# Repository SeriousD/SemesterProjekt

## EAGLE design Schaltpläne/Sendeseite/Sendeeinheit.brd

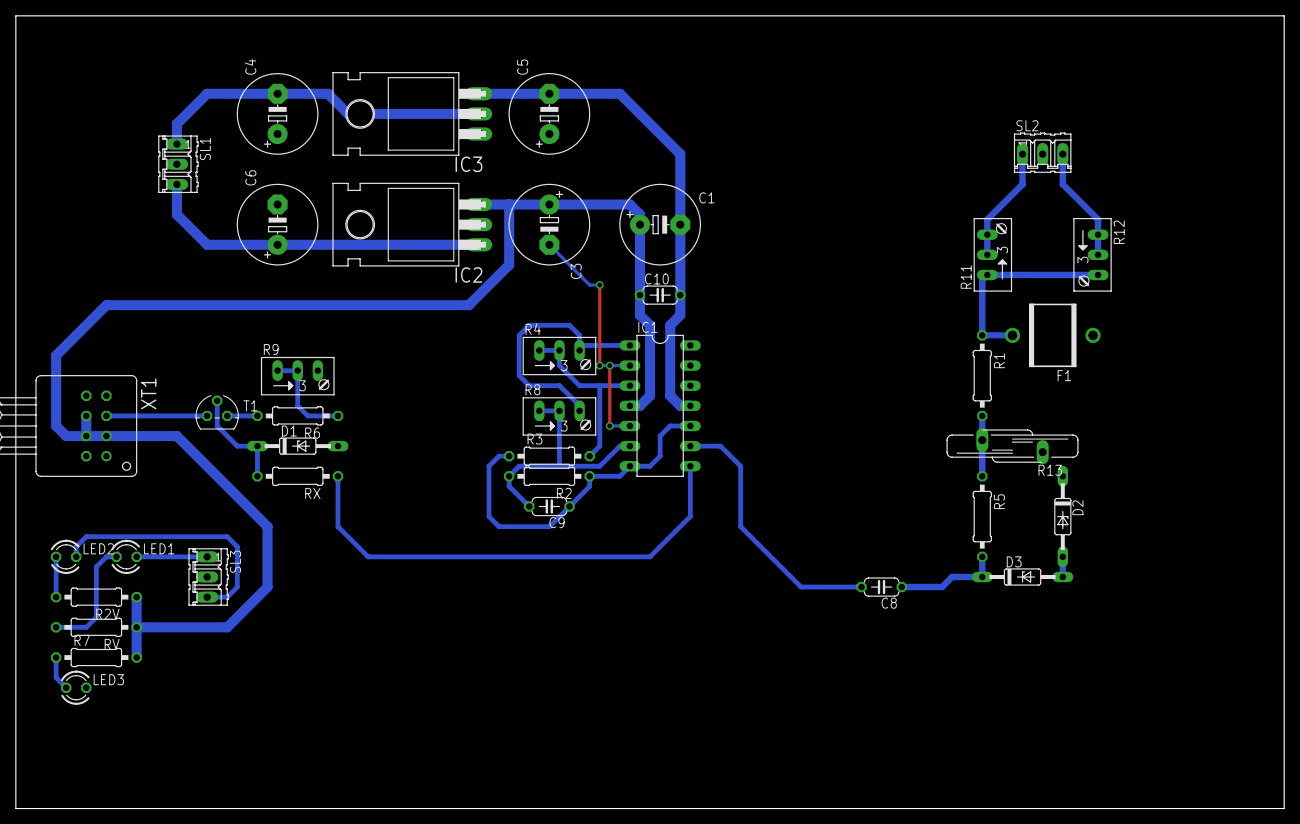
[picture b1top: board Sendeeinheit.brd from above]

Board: 2 copper layers, 160.0 x 100.0 mm, 38 parts (0 on the bottom side), 26 nets.

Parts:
C1: E5-10,5
C3, C5: 1µ; E5-10,5
C4: 300n; E5-10,5
C6: 330n; E5-10,5
C8, C10: C050-024X044
C9: 100n; C050-024X044
D1: DO35Z10
D2, D3: 7,5; DO35Z10
F1: EPCOS_N81
IC1: TL074P; DIL14
IC2: 7805T; TO220H
IC3: 7905T; TO220H
LED1, LED2, LED3: LED3MM
R1, R5: 1k; 0207/10
R2: 1M; 0207/10
R2V, R6, R7: 0207/10
R3: 50k; 0207/10
R4: 100k; RJ9W
R8: 5k; RJ9W
R9: RJ9W
R11: 50k; RJ9W
R12: 20k; RJ9W
R13: S14K11
RV: 0207/10
RX: 0207/10
SL1, SL2, SL3: 03P
T1: BC547; TO92
XT1: HFBR-1412; HFBR-X41X

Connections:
+5V: C1.+, C3.+, C10.1, IC1.4, IC2.3, R2V.1, R7.2, RV.1, XT1.2, XT1.6, XT1.7
-5V: C1.-, C5.-, C10.2, IC1.11, IC3.3
AC_IN: C8.2, IC1.9
GND: C3.-, C4.+, C5.+, C6.-, D1.A, D2.C, F1.1, IC1.2, IC1.5, IC2.2, IC3.1, LED3.K, R9.A, R13.1, SL1.2, SL2.2, SL3.2
unnamed: C6.+, IC2.1, SL1.3
unnamed: C4.-, IC3.2, SL1.1
unnamed: R12.E, R12.S, SL2.3
unnamed: R11.A, R11.S, SL2.1
unnamed: F1.2, R1.1, R11.E, R12.A
unnamed: D2.A, D3.A
unnamed: R1.2, R5.1, R13.2
unnamed: C8.1, D3.C, R5.2
unnamed: C9.2, IC1.6, R2.2, R8.E, R8.S
unnamed: LED2.K, SL3.3
unnamed: LED1.K, SL3.1
unnamed: LED2.A, R2V.2
unnamed: LED1.A, RV.2
unnamed: LED3.A, R7.1
unnamed: IC1.1, R4.A, R8.A
unnamed: IC1.3, R3.2, R4.E, R4.S
unnamed: T1.3, XT1.3
unnamed: D1.C, RX.2, T1.2
unnamed: R6.2, T1.1
unnamed: R6.1, R9.E, R9.S
PWM: IC1.8, RX.1
TRIANGLE: C9.1, IC1.7, IC1.10, R2.1, R3.1

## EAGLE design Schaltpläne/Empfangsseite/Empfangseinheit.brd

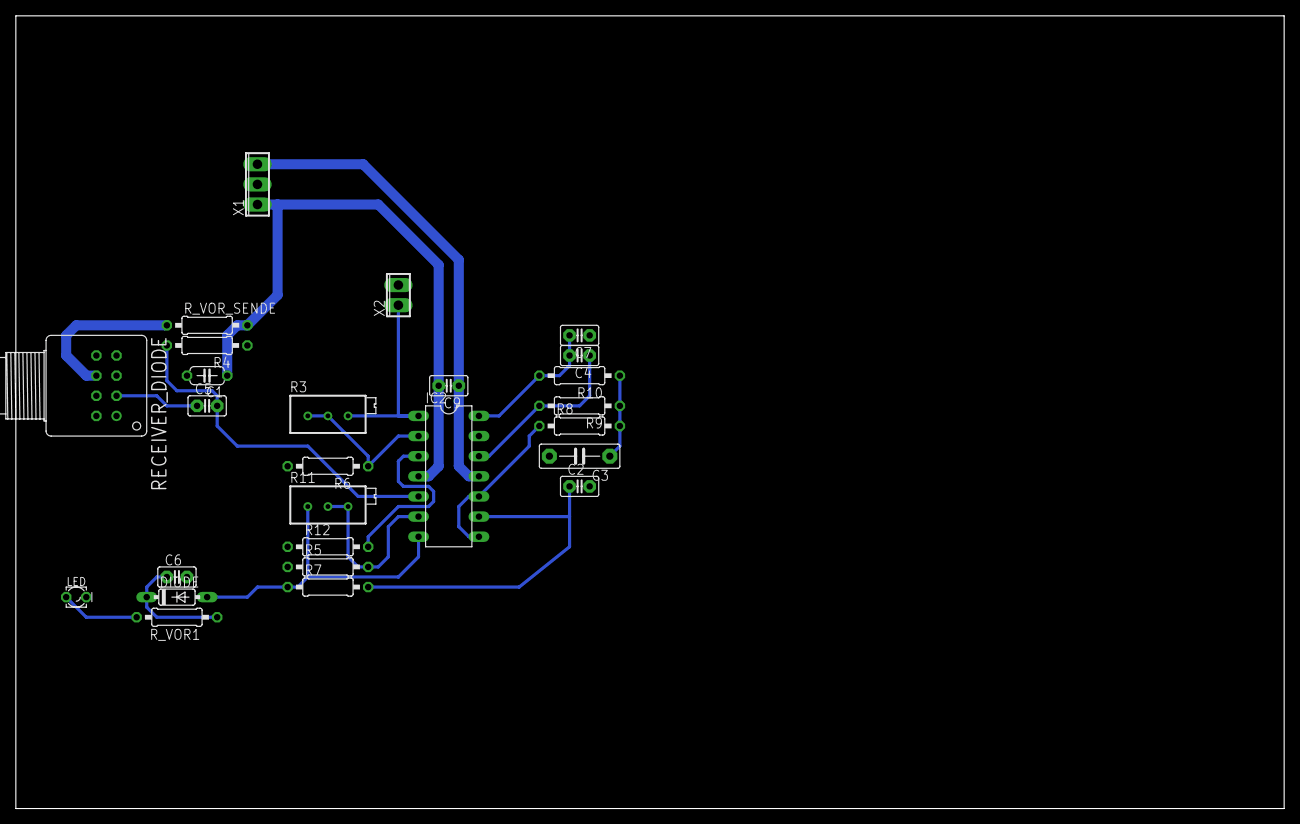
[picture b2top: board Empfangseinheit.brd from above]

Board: 2 copper layers, 160.0 x 100.0 mm, 26 parts (0 on the bottom side), 18 nets.

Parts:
C1: 22pF; C050-024X044
C2, C4, C5, C7, C9: 100nF; C2.5-2
C3: 1µF; C7.5B3
C6: 1µF; C2.5-2
DIODE: DIODE_DO35-7
IC2: TL074P; DIL14
LED: LED_LD260
R3: 50k; RTRIMT93XA
R4: 33k; 0207/10
R5, R6: 1k; 0207/10
R7: 15k; 0207/10
R8, R10: 6,8k; 0207/10
R9: 4,7k; 0207/10
R11: 500k; RTRIMT93XA
R12: 1M; 0207/10
RECEIVER_DIODE: HFBR-2416
R_VOR1: 33; 0207/10
R_VOR_SENDE: 10; 0207/10
X1: +5V,0V,-5V; 3POL254
X2: 2POL254

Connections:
FINAL_OUTPUT: IC2.1, R3.3, X2.1
FINAL_SIGNAL: IC2.2, R3.1, R3.2, R6.1
GND: C1.2, C2.2, C3.2, C6.2, IC2.13, LED.K, R4.1, R5.1, R6.2, R12.1, RECEIVER_DIODE.3, RECEIVER_DIODE.7, X1.2, X2.2
unnamed: C3.1, R8.2, R9.1, R10.1
unnamed: C4.1, IC2.12, R9.2
unnamed: C5.1, RECEIVER_DIODE.2
unnamed: IC2.6, R5.2, R11.2, R11.3
unnamed: C5.2, IC2.5, R4.2
unnamed: C2.1, IC2.9, R7.2
unnamed: C6.1, DIODE.C, R_VOR1.1
unnamed: RECEIVER_DIODE.6, R_VOR_SENDE.1
unnamed: C7.1, IC2.3, R12.2
unnamed: IC2.8, IC2.10, R8.1
unnamed: LED.A, R_VOR1.2
POST_AMP: DIODE.A, IC2.7, R7.1, R11.1
POST_FILTER: C4.2, C7.2, IC2.14, R10.2
V+: C1.1, C9.2, IC2.4, R_VOR_SENDE.2, X1.1
V-: C9.1, IC2.11, X1.3

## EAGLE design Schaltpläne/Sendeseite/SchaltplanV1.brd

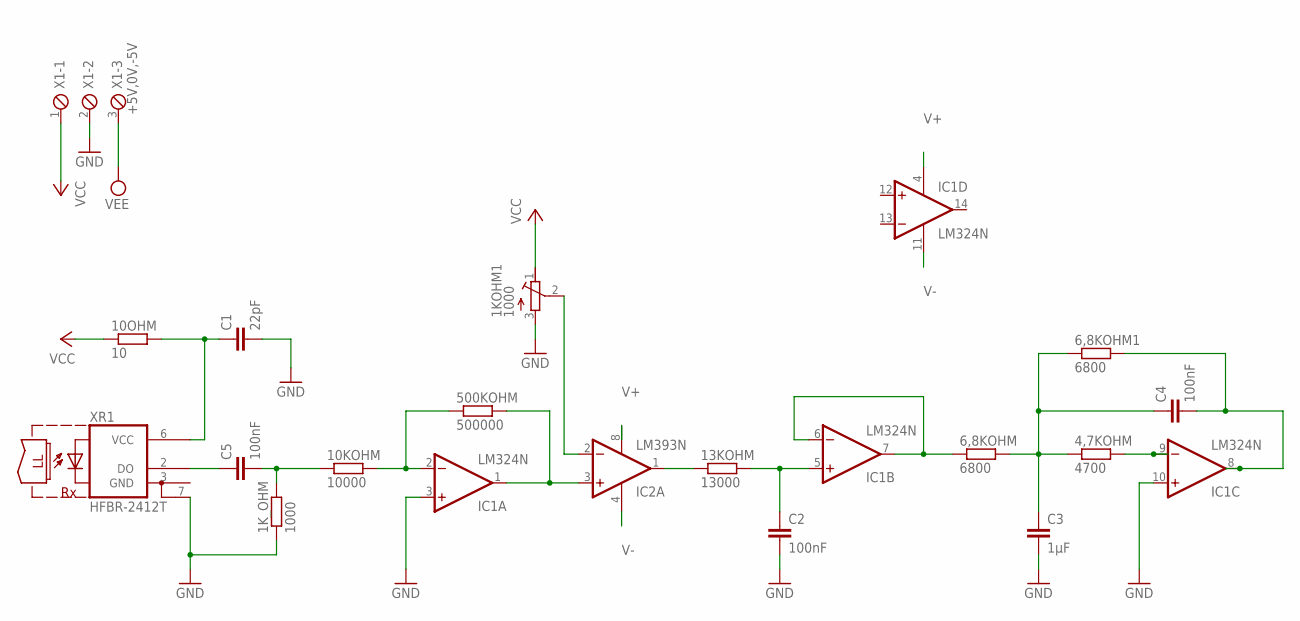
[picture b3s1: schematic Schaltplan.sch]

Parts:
1KOHM1: 1000; RTRIMT93XA
1K_OHM: 1000; 0309/12
4,7KOHM: 4700; 0309/12
6,8KOHM, 6,8KOHM1: 6800; 0309/12
10KOHM: 10000; 0309/12
10OHM: 10; 0309/12
13KOHM: 13000; 0309/12
500KOHM: 500000; 0309/12
C1: 22pF; C050-024X044
C2, C4, C5: 100nF; C2.5-2
C3: 1µF; C7.5B3
IC1: LM324N; DIL14
IC2: LM393N; DIL08
X1: +5V,0V,-5V; 3POL254
XR1: HFBR-2412T; HFBR-X41XT

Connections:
GND: 1KOHM1.3 (E), 1K_OHM.1, C1.2, C2.2, C3.2, IC1.3 (+IN), IC1.10 (+IN), X1.2, XR1.3 (GND), XR1.7 (GND1)
unnamed: 4,7KOHM.1, 6,8KOHM.2, 6,8KOHM1.1, C3.1, C4.1
unnamed: 4,7KOHM.2, IC1.9 (-IN)
unnamed: C5.1, XR1.2 (DO)
unnamed: 10OHM.2, C1.1, XR1.6 (VCC)
unnamed: 1K_OHM.2, 10KOHM.1, C5.2
unnamed: 500KOHM.2, IC1.1 (OUT), IC2.3 (+IN)
unnamed: 1KOHM1.2 (S), IC2.2 (-IN)
unnamed: 13KOHM.1, IC2.1 (OUT)
unnamed: 10KOHM.2, 500KOHM.1, IC1.2 (-IN)
unnamed: 13KOHM.2, C2.1, IC1.5 (+IN)
unnamed: 6,8KOHM.1, IC1.6 (-IN), IC1.7 (OUT)
unnamed: 6,8KOHM1.2, C4.2, IC1.8 (OUT)
V+: 1KOHM1.1 (A), 10OHM.1, IC1.4 (V+), IC2.8 (V+), X1.1
V-: IC1.11 (V-), IC2.4 (V-), X1.3

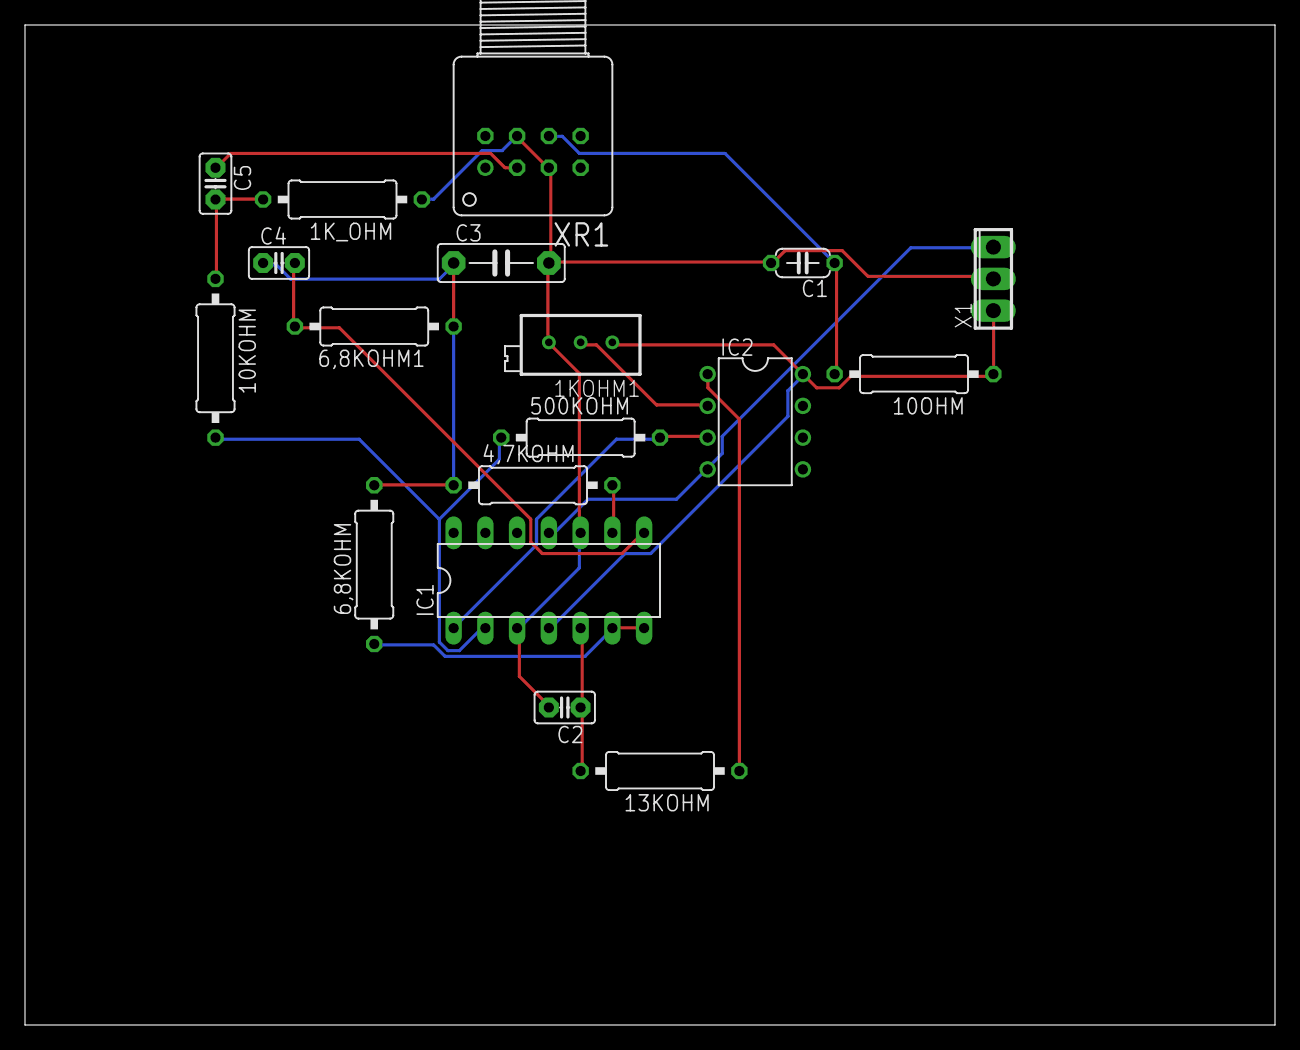
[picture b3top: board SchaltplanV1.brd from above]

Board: 2 copper layers, 100.0 x 80.0 mm, 18 parts (0 on the bottom side), 15 nets.

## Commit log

2016-11-13 First Commit
    Better documentation
    all files texyfied as far as possible
2016-11-13 simulationen
    meins und deins <3
2016-11-13 Added Schematics
    Dunno which..
2016-11-16 added schematic, and new simulation version
    new TL074 include to ensure the simulation won't fail because of false includes. still takes too long to simulate
2017-02-09 I <3 Cleo
    Because we have the same mental illness :)
2017-05-02 updated schematics
    Rx,Tx
2017-05-03 added Screens
    OSZI_SCREENS IN GFX
2017-05-04 add final Tx schematic
2017-05-04 Schematics updated
    Empfangseinheit baby
2017-05-09 Anleitung finished
2017-05-15 added csv's
2017-05-25 fuse branches
    keep Anleitung up to date
2017-05-26 bestimmtheitsmaß
    berechnung per excel, formeln kommen im späteren commit
2017-05-27 add Kal
2017-05-27 fix simulations
2017-05-27 add oszi screens and inside photo
2017-05-27 add justification
2017-05-27 add references
2017-05-27 do something I dont know
2017-05-27 add ignore file
2017-05-27 edited justierung.tex
    added bestimmtheitsmaß
2017-05-28 updated TODO list & justierung.tex
    justierung.tex only needs a little Dennis magic to be FINISHED
2017-05-29 fix merge problems
2017-05-29 improve plot&calc
    prettier plots, automatic CSV loading etc.
2017-05-30 add sexy plots
2017-05-30 delete obsolete files
    since there are new sexy plots, the old errorous plots aren't needed anymore. Also deleted old wrong copied folders and files
2017-05-30 move graphics to right folder
    these files were in the base folder but belong in the gfx folder, stored for later use
2017-05-30 update sexy plots and modify plot script
    another part in the plot script were needed for the pwm area graphic
2017-05-30 improve file for typography
    This commit will reduce the warings and errors of LaTeX massively and will improve the overall look of hte document
2017-05-30 fix LaTeX Errors
    The file had errorous contents, removed double "\\"
2017-06-11 calculation of the coefficient of determination
    all calculations done, AGAIN (no rescue was successful)
2017-06-11 updated justierung.tex
    added calculations of the coefficient of determination to the tables
2017-07-25 hopefully be the last
